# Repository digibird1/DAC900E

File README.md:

# DAC900E
Breakout board for the DAC900E from Texas Instruments a 165 MSPS @ 10 Bit DAC, to connect to the DE0 from ALTERA

http://www.ti.com/lit/ds/symlink/dac900.pdf

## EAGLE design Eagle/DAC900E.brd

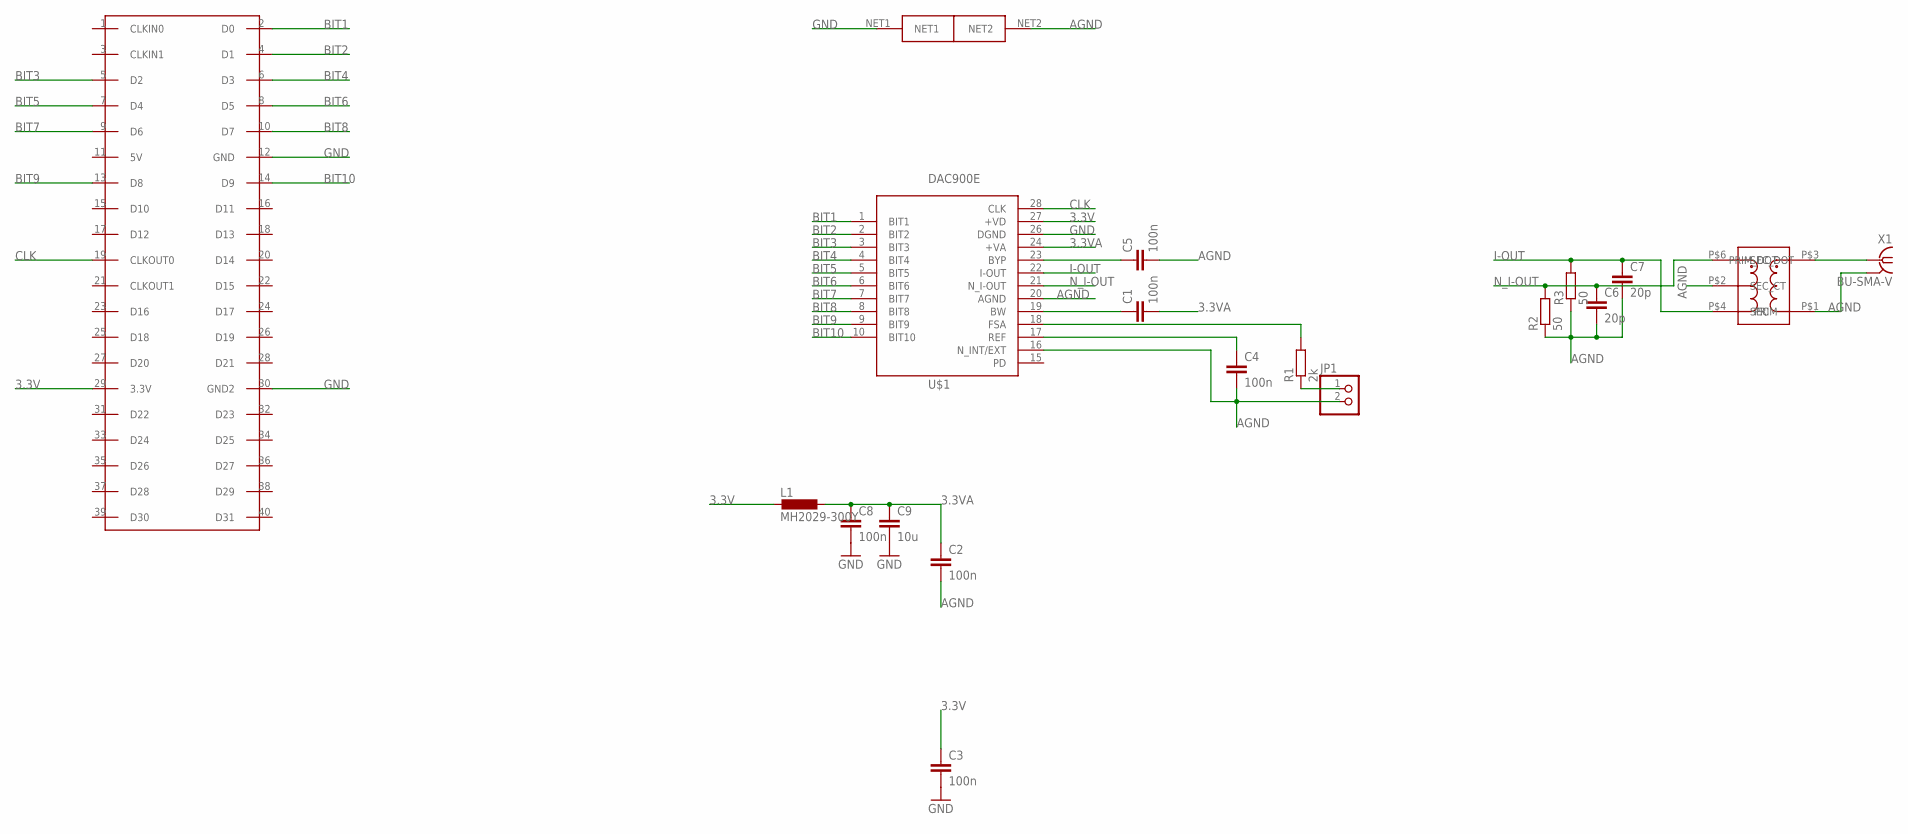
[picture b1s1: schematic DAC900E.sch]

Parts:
C1, C2, C3, C4, C5, C8: 100n; C0805
C6, C7: 20p; C0805
C9: 10u; C0805
JP1: PINHD-1X2; 1X02
L1: MH2029-300Y; R0805
R1: 2k; R0805
R2, R3: 50; R0805
U$1: DAC900E; TSSOP28
U$2: NET_TIE; NET-TIE
U$3: FPGA_GPIO_DE0; 2X20
U$4: ADT1-1WT; CD542
X1: BU-SMA-V

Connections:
3.3V: C3.1, L1.2, U$1.27 (+VD), U$3.29 (3.3V)
3.3VA: C1.2, C2.1, C8.1, C9.1, L1.1, U$1.24 (+VA)
AGND: C2.2, C4.2, C5.2, C6.2, C7.2, JP1.2, R2.1, R3.1, U$1.16 (N_INT/EXT), U$1.20 (AGND), U$2.NET2, U$4.P$1 (PRIM), U$4.P$2 (SEC_CT), X1.2, X1.3 (2), X1.4 (2), X1.5 (2)
BIT1: U$1.1 (BIT1), U$3.2 (D0)
BIT2: U$1.2 (BIT2), U$3.4 (D1)
BIT3: U$1.3 (BIT3), U$3.5 (D2)
BIT4: U$1.4 (BIT4), U$3.6 (D3)
BIT5: U$1.5 (BIT5), U$3.7 (D4)
BIT6: U$1.6 (BIT6), U$3.8 (D5)
BIT7: U$1.7 (BIT7), U$3.9 (D6)
BIT8: U$1.8 (BIT8), U$3.10 (D7)
BIT9: U$1.9 (BIT9), U$3.13 (D8)
BIT10: U$1.10 (BIT10), U$3.14 (D9)
CLK: U$1.28 (CLK), U$3.19 (CLKOUT0)
GND: C3.2, C8.2, C9.2, U$1.26 (DGND), U$2.NET1, U$3.12 (GND), U$3.30 (GND2)
I-OUT: C7.1, R3.2, U$1.22 (I-OUT), U$4.P$4 (SEC)
unnamed: JP1.1, R1.1
unnamed: U$4.P$3 (PRIM_DOT), X1.1
unnamed: C5.1, U$1.23 (BYP)
unnamed: C1.1, U$1.19 (BW)
unnamed: R1.2, U$1.18 (FSA)
unnamed: C4.1, U$1.17 (REF)
N_I-OUT: C6.1, R2.2, U$1.21 (N_I-OUT), U$4.P$6 (SEC_DOT)

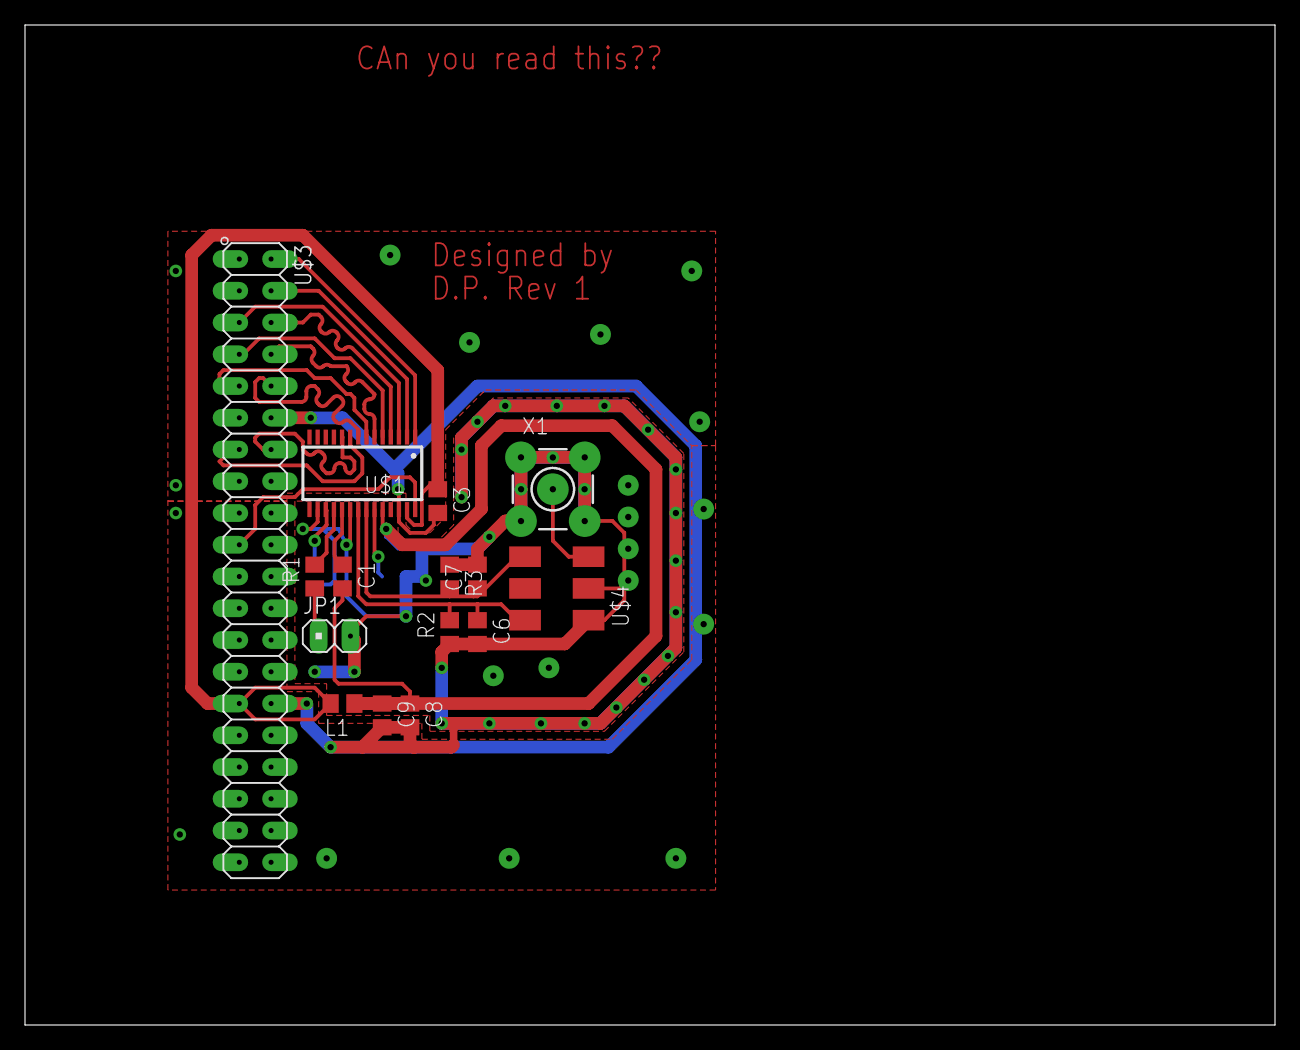
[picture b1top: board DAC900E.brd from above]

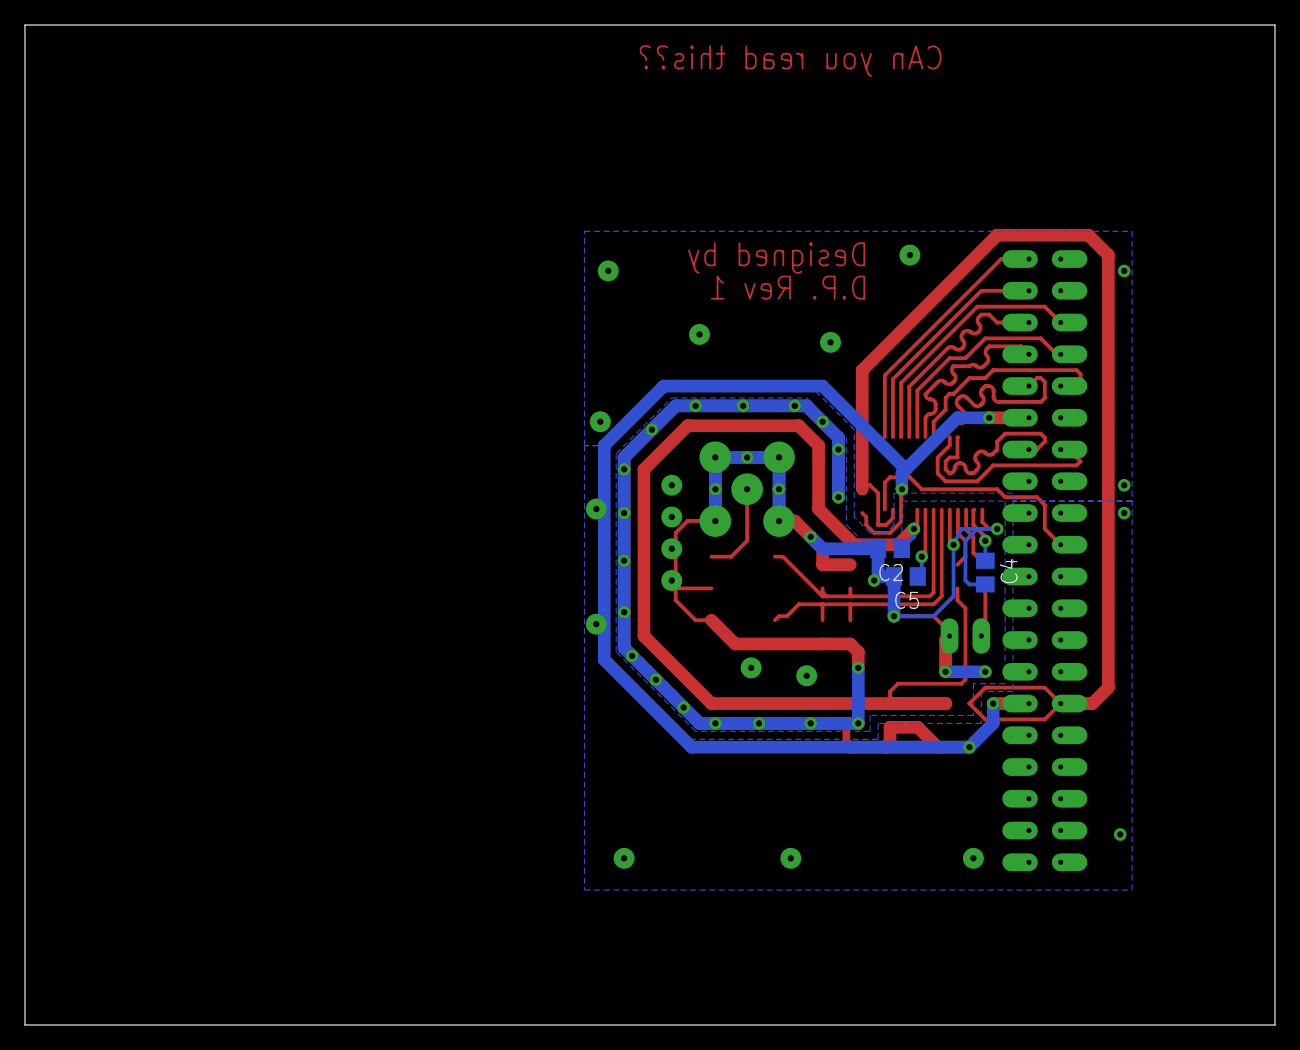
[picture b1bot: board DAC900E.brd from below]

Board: 2 copper layers, 100.0 x 80.0 mm, 19 parts (3 on the bottom side), 23 nets.

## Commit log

2015-04-01 Eagle PCB files
2015-04-01 Create README.md
    Breakout board for the DAC900E from Texas Instruments a 165 MSPS @ 10 Bit DAC, to connect to the DE0 from ALTERA
    http://www.ti.com/lit/ds/symlink/dac900.pdf
